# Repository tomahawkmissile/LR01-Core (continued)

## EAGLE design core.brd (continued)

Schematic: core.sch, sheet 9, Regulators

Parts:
C4, C36, C37, C38, C42, C43, C162, C175, C181: 10uF; 0603
C5, C7, C8, C12, C46, C47, C87, C152, C153, C164, C182, C184, C185, C192, C195: 0.1uF; 0603
C6, C176, C183, C198, C199: 22uF; 0603
C34, C35: 150uF; CAPPRD350W65D800H1500B
C39, C40: 1nF; 0603
C41, C45, C148, C149: 4.7uF; 0603
C44: 0.033uF; 0603
C86, C151, C163, C191: 1uF; 0603
C142, C145: 470uF; CAPPRD300W65D800H1200B
C143, C144: 270uF; CAPPRD350W65D800H1500B
C146: 220uF; CAPPRD250W65D600H1100B
C150, C167: 0.47uF; 0603
C154, C172: 100pF; 0603
C155, C165, C173: 0.01uF; 0603
C156, C171: 0.056uF; 0603
C157, C161, C174: 47uF; 0805
C159: 100uF; 0805
C166, C168: 2.2uF; 0603
C169, C170: 33pF; 0603
C193: 10uF; 0805
C194: 0.1uF; 0805
C196: 0.015uF; 0603
C197: 150pF; 0603
C200: 200pF; 0603
C216: DNI; 0603
D5, D6: Green; 0603.LED
Q8, Q9, Q10, Q11: CSD18543Q3A; SON65P300X315X90-9N
R13: 5.11R; 0603
R14: 7.15k; 0603
R15, R208, R230, R243: 100k; 0603
R16: 0.006R; 0805
R17: 3.09R; 0603
R18: DNI; 0603
R19, R20: 4.75k; 0603
R52, R229: 10k; 0603
R54: 4.7k; 0603
R202, R203, R204, R211, R212, R213: 10.2R; 0603
R205, R217: 0.005R; R2512
R206: 0R; 0603
R207: 19.6k 0.1%; 0603
R214, R215, R216: 49.9R; 0603
R218: 29.4k 1%; 0603
R219: 220R; 0603
R220: 330R; 0603
R231: 2.05k_1%; 0603
R232: 51.1R_1%; 0603
R233: 31.6k_1%; 0603
R234: 10k_1%; 0603
TP1, TP2, TP24, TP25, TP26, TP29, TP31, TP32: TESTPAD_TPSQB1,27; TESTPAD_B1,27
U4, U38: Value; YZH0016AFAF
U6: TPS51116_PWP_20; PWP20_3P4X2P4
U11, U40: Value; DRV0006A
U34: Value; RWG0040A
U35: Value; RLT0007A
U41: Value; DRC0010J
U$1, U$28, U$30: XFL4015-471MEB
U$2: IRF7821; SOIC127P600X175-8_V2
U$3: IRF7832; SOIC127P600X175-8_V2
U$4: XFL4020-102MEB
U$20, U$21: DB2441700L
U$22, U$25: XEL6030-152MEB
U$33: XEL4030-682ME_

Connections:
DDR_VREF: C44.2, U6.7 (VTTREF); also elsewhere on the board
DDR_VTT: C42.2, C43.2, U6.2 (VTT), U6.4 (VTTSNS); also elsewhere on the board
unnamed: U4.B3 (SW_2), U4.B4 (SW), U$1.P$1
unnamed: R19.1, R20.2, U6.10 (VDDQSET)
unnamed: C12.1, U6.20 (VBST)
unnamed: U6.17 (DRVL), U$3.4 (GATE)
unnamed: R13.1, U6.19 (DRVH)
unnamed: R13.2, U$2.4 (GATE)
unnamed: C12.2, U6.18 (LL), U$2.1 (SOURCE), U$2.2 (SOURCE), U$2.3 (SOURCE), U$3.5 (DRAIN), U$3.6 (DRAIN), U$3.7 (DRAIN), U$3.8 (DRAIN), U$4.V
unnamed: C39.2, R14.1, U6.15 (CS)
unnamed: C40.1, R16.2, R18.2, U$3.1 (SOURCE), U$3.2 (SOURCE), U$3.3 (SOURCE)
unnamed: C40.2, R17.1
unnamed: C151.2, U34.32 (RES)
unnamed: C152.1, U34.20 (HB1), U$21.CATHODE
unnamed: C153.2, U34.11 (HB2), U$20.CATHODE
unnamed: C152.2, Q8.1 (S), Q8.2 (S), Q8.3 (S), Q9.5-9 (D), U34.21 (SW1), U$22.P$2
unnamed: Q8.4 (G), R202.1, U34.23 (HOL1)
unnamed: R202.2, U34.22 (HO1)
unnamed: Q9.4 (G), R203.1, R204.1
unnamed: R203.2, U34.18 (LO1)
unnamed: R204.2, U34.19 (LOL1)
unnamed: R205.2, R214.2, U$22.P$1
unnamed: C169.1, R214.1, U34.27 (CS1)
unnamed: C169.2, R206.1, U34.26 (VOUT1)
unnamed: C154.2, R207.2, U34.29 (COMP1)
unnamed: C155.2, R207.1
unnamed: C156.2, U34.30 (SS1)
unnamed: C153.1, Q10.5-9 (D), Q11.1 (S), Q11.2 (S), Q11.3 (S), U34.10 (SW2), U$25.P$1
unnamed: Q11.4 (G), R211.1, U34.8 (HOL2)
unnamed: R211.2, U34.9 (HO2)
unnamed: R212.1, U34.12 (LOL2)
unnamed: R213.1, U34.13 (LO2)
unnamed: Q10.4 (G), R212.2, R213.2
unnamed: R215.2, R217.1, U$25.P$2
unnamed: C170.2, R215.1, U34.4 (CS2)
unnamed: C170.1, R216.1, U34.5 (VOUT2)
unnamed: C171.2, U34.1 (SS2)
unnamed: C173.1, R218.2
unnamed: C172.1, R218.1, U34.2 (COMP2)
unnamed: D6.P$1 (1), R219.2
unnamed: D5.P$1 (1), R220.2
unnamed: U35.6 (SW), U$28.P$1
unnamed: U38.B3 (SW_2), U38.B4 (SW), U$30.P$1
unnamed: C195.2, U41.2 (PH), U$33.P$1
unnamed: C195.1, U41.9 (BOOT)
unnamed: C196.1, R231.2
unnamed: C197.1, R231.1, U41.7 (COMP)
unnamed: C200.2, R232.1, R233.2
RESET_SOC_MPU: C8.1, C185.1, U4.D1 (VDD), U38.D1 (VDD); also elsewhere on the board
SOC_CORE: C183.2, C184.2, TP29.TP, U$30.P$2; also elsewhere on the board
SOC_I2C0_SCL: U38.D3 (SCL); also elsewhere on the board
SOC_I2C0_SDA: U38.D2 (SDA); also elsewhere on the board
SOC_I2C2_SCL: U4.D3 (SCL); also elsewhere on the board
SOC_I2C2_SDA: U4.D2 (SDA); also elsewhere on the board
SOC_MPU: C6.2, C7.2, TP1.TP, U$1.P$2; also elsewhere on the board
TPS54334_VSENSE: C200.1, R233.1, R234.2, U41.6 (VSENSE)
VCC_1V5_DDR: C34.1 (+), C35.1 (+), C38.2, R17.2, R19.2, U6.1 (VLDOIN), U6.6 (MODE), U6.9 (VDDQSNS), U$4.V1; also elsewhere on the board
VCC_1V8: C176.2, TP26.TP, U35.3 (FB), U35.4 (VOS), U$28.P$2; also elsewhere on the board
VCC_1V8_PG: R54.1, U6.11 (S3), U6.12 (S5), U35.2 (PG)
VCC_3V3_IO: C198.2, C199.2, R232.2, TP32.TP, U$33.P$2; also elsewhere on the board
VCC_3V3_PREREG: C4.2, C5.2, C142.1 (+), C143.1 (+), C157.2, C175.2, C181.2, C182.2, R52.2, R54.2, R205.1, R206.2, R208.2, R219.1, R229.2, R230.2, TP24.TP, U4.A1 (AVIN), U4.A3 (VSEL1), U4.A4 (VIN), U4.C2 (VSEL0), U11.6 (IN), U35.7 (VIN), U38.A1 (AVIN), U38.A3 (VSEL1), U38.A4 (VIN), U38.C2 (VSEL0), U40.6 (IN); also elsewhere on the board
VCC_3V3_PREREG_PG: C165.2, R208.1, U34.24 (PG1)
VCC_5V0: C39.1, C41.2, C45.2, C46.2, C47.2, C144.1 (+), C145.1 (+), C174.2, R14.2, R15.2, R216.2, R217.2, R220.1, TP25.TP, U6.8 (COMP), U6.14 (V5IN), U34.6 (VCCX); also elsewhere on the board
VCC_5V0_PG: R243.2, U34.7 (PG2)
VCC_12V0: C36.2, C37.2, C146.1 (+), C159.2, C161.2, C162.2, C163.2, C164.2, C166.1, C167.1, C168.1, C193.2, C194.2, Q8.5-9 (D), Q11.5-9 (D), U34.25 (VIN), U34.31 (EN1), U34.40 (EN2), U41.1 (VIN), U$2.5 (DRAIN), U$2.6 (DRAIN), U$2.7 (DRAIN), U$2.8 (DRAIN); also elsewhere on the board
VCC_LM5140: C148.2, C149.2, U34.15 (VCC_2), U34.16 (VCC), U$20.ANODE, U$21.ANODE
VDDA_1V8: C191.1, TP31.TP, U40.1 (OUT); also elsewhere on the board
VDDA_1V8_PG: C192.1, R229.1, U40.3 (PG)
VDDA_LM5140: C150.1, R243.1, U34.3 (FB2), U34.28 (FB1), U34.33 (DEMB), U34.34 (ILSET), U34.36 (VDDA), U34.37 (OSC)
VDDS_DDR_PGOOD: R15.1, U6.13 (PGOOD), U41.8 (EN)
VDD_CORE: U38.B1 (SENSE+); also elsewhere on the board
VDD_MPU: U4.B1 (SENSE+); also elsewhere on the board
VDD_RTC: C86.1, TP2.TP, U11.1 (OUT); also elsewhere on the board
VDD_RTC_PG: C87.1, R52.1, U11.3 (PG), U35.1 (EN), U40.4 (EN)
VIN_MON_PORZ_3V3_PG: C216.2, R230.1, U4.B2 (EN), U11.4 (EN), U38.B2 (EN), U41.10 (PGOOD); also elsewhere on the board
VSS: C4.1, C5.1, C6.1, C7.1, C8.2, C34.2 (-), C35.2 (-), C36.1, C37.1, C38.1, C41.1, C42.1, C43.1, C44.1, C45.1, C46.1, C47.1, C86.2, C87.2, C142.2 (-), C143.2 (-), C144.2 (-), C145.2 (-), C146.2 (-), C148.1, C149.1, C150.2, C151.1, C154.1, C155.1, C156.1, C157.1, C159.1, C161.1, C162.1, C163.1, C164.1, C165.1, C166.2, C167.2, C168.2, C171.1, C172.2, C173.2, C174.1, C175.1, C176.1, C181.1, C182.1, C183.1, C184.1, C185.2, C191.2, C192.2, C193.1, C194.1, C196.2, C197.2, C198.1, C199.1, C216.1, D5.P$2 (2), D6.P$2 (2), Q9.1 (S), Q9.2 (S), Q9.3 (S), Q10.1 (S), Q10.2 (S), Q10.3 (S), R16.1, R18.1, R20.1, R234.1, U4.A2 (AGND), U4.C1 (SENSE-), U4.C3 (PGND_2), U4.C4 (PGND_3), U4.D4 (PGND), U6.3 (VTTGND), U6.5 (GND), U6.16 (PGND), U6.21 (EPAD), U11.5 (GND), U11.7 (PAD), U34.14 (PGND2), U34.17 (PGND1), U34.35 (AGND), U34.38 (SYN_IN), U34.41 (DAP), U35.5 (GND), U38.A2 (AGND), U38.C1 (SENSE-), U38.C3 (PGND_2), U38.C4 (PGND_3), U38.D4 (PGND), U40.5 (GND), U40.7 (PAD), U41.3 (GND_2), U41.4 (GND_3), U41.5 (GND), U41.11 (PAD); also elsewhere on the board

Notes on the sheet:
TPS62363
TPS62087
LM5140
TPS54334
LP5912

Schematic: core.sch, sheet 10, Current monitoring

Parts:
C1, C2, C3, C9, C10, C11, C13, C29, C30, C31, C32, C33: 0.1uF; 0603
R1, R2, R4, R5, R7, R8, R10, R11: 10_1%; 0603
R3, R6, R9, R12: 0.002_1%; 1206
U3, U5, U7, U8: INA226_DGS_10; DGS10

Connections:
INA_ALERT: U3.3 (ALERT), U5.3 (ALERT), U7.3 (ALERT), U8.3 (ALERT); also elsewhere on the board
unnamed: C2.2, R2.1, U3.8 (VBUS), U3.9 (VIN-)
unnamed: C2.1, R1.1, U3.10 (VIN+)
unnamed: C10.2, R5.1, U5.8 (VBUS), U5.9 (VIN-)
unnamed: C10.1, R4.1, U5.10 (VIN+)
unnamed: C29.2, R8.1, U7.8 (VBUS), U7.9 (VIN-)
unnamed: C29.1, R7.1, U7.10 (VIN+)
unnamed: C32.2, R11.1, U8.8 (VBUS), U8.9 (VIN-)
unnamed: C32.1, R10.1, U8.10 (VIN+)
SOC_CORE: C3.1, R1.2, R3.1; also elsewhere on the board
SOC_I2C0_SCL: U3.5 (SCL), U5.5 (SCL), U7.5 (SCL), U8.2 (A0), U8.5 (SCL); also elsewhere on the board
SOC_I2C0_SDA: U3.4 (SDA), U5.4 (SDA), U7.2 (A0), U7.4 (SDA), U8.4 (SDA); also elsewhere on the board
SOC_MPU: C11.1, R4.2, R6.1; also elsewhere on the board
SOC_VDDS_DDR: R11.2, R12.2; also elsewhere on the board
VCC_1V5_DDR: C30.1, C33.1, R7.2, R9.1, R10.2, R12.1; also elsewhere on the board
VCC_3V3_IO: C1.2, C9.2, C13.2, C31.2, U3.6 (VS), U5.1 (A1), U5.6 (VS), U7.6 (VS), U8.6 (VS); also elsewhere on the board
VDDS_DDR: R8.2, R9.2; also elsewhere on the board
VDD_CORE: R2.2, R3.2; also elsewhere on the board
VDD_MPU: R5.2, R6.2; also elsewhere on the board
VSS: C1.1, C3.2, C9.1, C11.2, C13.1, C30.2, C31.1, C33.2, U3.1 (A1), U3.2 (A0), U3.7 (GND), U5.2 (A0), U5.7 (GND), U7.1 (A1), U7.7 (GND), U8.1 (A1), U8.7 (GND); also elsewhere on the board

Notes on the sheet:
I2C Address=0x40
I2C Address=0x41
I2C Address=0x42
I2C Address=0x43

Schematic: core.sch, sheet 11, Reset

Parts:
C574, C578, C579: 0.1uF; 0402
C575: 0.01uF; 0402
C577: DNI; 0402
R72: 1k; 0402
R536: 261k_1%; 0402
R537, R538, R541, R542: 10k_1%; 0402
R540: 5.81k_1%; 0402
R543: 0R; 0402
TP14: TESTPAD_TPSQB1,27; TESTPAD_B1,27
U76: Value; DDC0006A_N
U77: TPS3897_DRY_6; DRY6
U78: SN74LVC1G11_DCK_6; DCK6

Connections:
!JTAG_TRST: U78.6 (C); also elsewhere on the board
!SUPERVISOR_MASTER_RESET: R72.1, U77.1 (ENABLE); also elsewhere on the board
unnamed: C575.1, R536.1, R537.2, U76.3 (SENSE)
unnamed: C577.1, U77.5 (CT)
unnamed: R543.1, U78.4 (Y)
unnamed: R540.1, R541.2, U77.3 (SENSE)
SOC_PORZ: R543.2, TP14.TP; also elsewhere on the board
SOC_POWER_MON_PORZ: R542.1, U77.4 (SENSE_OUT), U78.1 (A)
VCC_3V3_IO: C579.1, R538.2, R542.2, U78.5 (VCC); also elsewhere on the board
VCC_3V3_PREREG: C578.2, R72.2, U77.6 (VCC); also elsewhere on the board
VCC_12V0: C574.2, R536.2, U76.5 (VDD); also elsewhere on the board
VDD_MPU: R540.2; also elsewhere on the board
VIN_MON_PORZ_3V3_PG: R538.1, U76.1 (OUT), U78.3 (B); also elsewhere on the board
VSS: C574.1, C575.2, C577.2, C578.1, C579.2, R537.1, R541.1, U76.2 (GND_2), U76.4 (GND_3), U76.6 (GND), U77.2 (GND), U78.2 (GND); also elsewhere on the board

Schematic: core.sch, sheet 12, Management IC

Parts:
C117: 0.1uF; 0402
R55, R90, R91, R94, R95, R96, R97: 10k; 0402
U12: TCA9555_RTW_24; RTW24_2P45X2P45

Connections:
!ETH_INT: R90.2, U12.2 (P01); also elsewhere on the board
!ETH_RESET: R91.2, U12.3 (P02); also elsewhere on the board
!MGMT_INT0: R94.2, U12.7 (P06); also elsewhere on the board
!MGMT_INT1: R95.2, U12.8 (P07); also elsewhere on the board
!MMC1_RESET: R97.2, U12.12; also elsewhere on the board
!MMC2_RESET: R96.2, U12.11; also elsewhere on the board
!NMI: R55.1, U12.22 (*INT); also elsewhere on the board
!USB0_OVERCURRENT: U12.4 (P03); also elsewhere on the board
!USB1_OVERCURRENT: U12.5 (P04); also elsewhere on the board
DCAN1_STB: U12.6 (P05); also elsewhere on the board
EXT_WAKEUP: U12.10; also elsewhere on the board
INA_ALERT: U12.1 (P00); also elsewhere on the board
RESET_SOC_MPU: U12.17; also elsewhere on the board
SOC_I2C0_SCL: U12.19 (SCL); also elsewhere on the board
SOC_I2C0_SDA: U12.20 (SDA); also elsewhere on the board
VCC_3V3_IO: C117.2, R55.2, R90.1, R91.1, R94.1, R95.1, R96.1, R97.1, U12.21 (VCC); also elsewhere on the board
VSS: C117.1, U12.9 (GND), U12.18 (A0), U12.23 (A1), U12.24 (A2), U12.25 (EPAD); also elsewhere on the board

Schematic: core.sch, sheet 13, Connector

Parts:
C147: 470uF; CAPPRD300W65D800H1200B
J1: SEAM-40-XX.X-XX-06-X-A

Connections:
!MGMT_INT0: J1.B26 (26); also elsewhere on the board
!MGMT_INT1: J1.B25 (25); also elsewhere on the board
!SUPERVISOR_MASTER_RESET: J1.B19 (19); also elsewhere on the board
!UART1_CTS: J1.C26 (26); also elsewhere on the board
!UART1_RTS: J1.C25 (25); also elsewhere on the board
!WARM_RESET: J1.C6 (6); also elsewhere on the board
DCAN1_H: J1.B17 (17); also elsewhere on the board
DCAN1_L: J1.B16 (16); also elsewhere on the board
EXT_WAKEUP: J1.C7 (7); also elsewhere on the board
GPIO1_16: J1.C17 (17); also elsewhere on the board
GPIO1_20: J1.C18 (18); also elsewhere on the board
GPIO1_21: J1.C19 (19); also elsewhere on the board
GPIO1_26: J1.C20 (20); also elsewhere on the board
GPIO1_27: J1.C21 (21); also elsewhere on the board
GPIO1_29: J1.C10 (10); also elsewhere on the board
GPIO2_4: J1.C9 (9); also elsewhere on the board
GPIO3_7: J1.C16 (16); also elsewhere on the board
GPIO3_8: J1.C15 (15); also elsewhere on the board
GPIO3_18: J1.C11 (11); also elsewhere on the board
GPIO3_19: J1.C12 (12); also elsewhere on the board
GPIO3_20: J1.C13 (13); also elsewhere on the board
GPIO3_21: J1.C14 (14); also elsewhere on the board
PWM0: J1.A30 (30); also elsewhere on the board
PWM1: J1.A31 (31); also elsewhere on the board
PWM2: J1.A32 (32); also elsewhere on the board
PWM3: J1.A33 (33); also elsewhere on the board
PWM4: J1.A34 (34); also elsewhere on the board
PWM5: J1.A35 (35); also elsewhere on the board
PWM6: J1.A36 (36); also elsewhere on the board
PWM7: J1.A37 (37); also elsewhere on the board
SOC_I2C2_SCL: J1.A40 (40); also elsewhere on the board
SOC_I2C2_SDA: J1.A39 (39); also elsewhere on the board
SPI0_CLK: J1.B12 (12); also elsewhere on the board
SPI0_CS0: J1.B13 (13); also elsewhere on the board
SPI0_MISO: J1.B14 (14); also elsewhere on the board
SPI0_MOSI: J1.B11 (11); also elsewhere on the board
SPI1_CLK: J1.C29 (29); also elsewhere on the board
SPI1_CS0: J1.C31 (31); also elsewhere on the board
SPI1_D0: J1.C30 (30); also elsewhere on the board
SPI1_D1: J1.C28 (28); also elsewhere on the board
TIMER4: J1.C1 (1); also elsewhere on the board
TIMER5: J1.C2 (2); also elsewhere on the board
TIMER6: J1.C3 (3); also elsewhere on the board
TIMER7: J1.C4 (4); also elsewhere on the board
UART1_RXD: J1.C24 (24); also elsewhere on the board
UART1_TXD: J1.C23 (23); also elsewhere on the board
VCC_3V3_IO: J1.B23 (23); also elsewhere on the board
VCC_5V0: J1.B21 (21); also elsewhere on the board
VCC_12V0: C147.1 (+), J1.A1 (1), J1.A2 (2), J1.A3 (3), J1.A4 (4), J1.A5 (5), J1.A6 (6), J1.A7 (7), J1.A8 (8), J1.A9 (9), J1.A10 (10); also elsewhere on the board
VSS: C147.2 (-), J1.A11 (11), J1.A12 (12), J1.A13 (13), J1.A14 (14), J1.A15 (15), J1.A16 (16), J1.A17 (17), J1.A18 (18), J1.A19 (19), J1.A20 (20), J1.A29 (29), J1.A38 (38), J1.B1 (1), J1.B2 (2), J1.B3 (3), J1.B4 (4), J1.B5 (5), J1.B6 (6), J1.B7 (7), J1.B8 (8), J1.B9 (9), J1.B10 (10), J1.B15 (15), J1.B18 (18), J1.B20 (20), J1.B22 (22), J1.B24 (24), J1.B27 (27), J1.B28 (28), J1.B29 (29), J1.B30 (30), J1.B31 (31), J1.B32 (32), J1.B33 (33), J1.B34 (34), J1.B35 (35), J1.B36 (36), J1.B37 (37), J1.B38 (38), J1.B39 (39), J1.B40 (40), J1.C5 (5), J1.C8 (8), J1.C22 (22), J1.C27 (27), J1.C32 (32); also elsewhere on the board

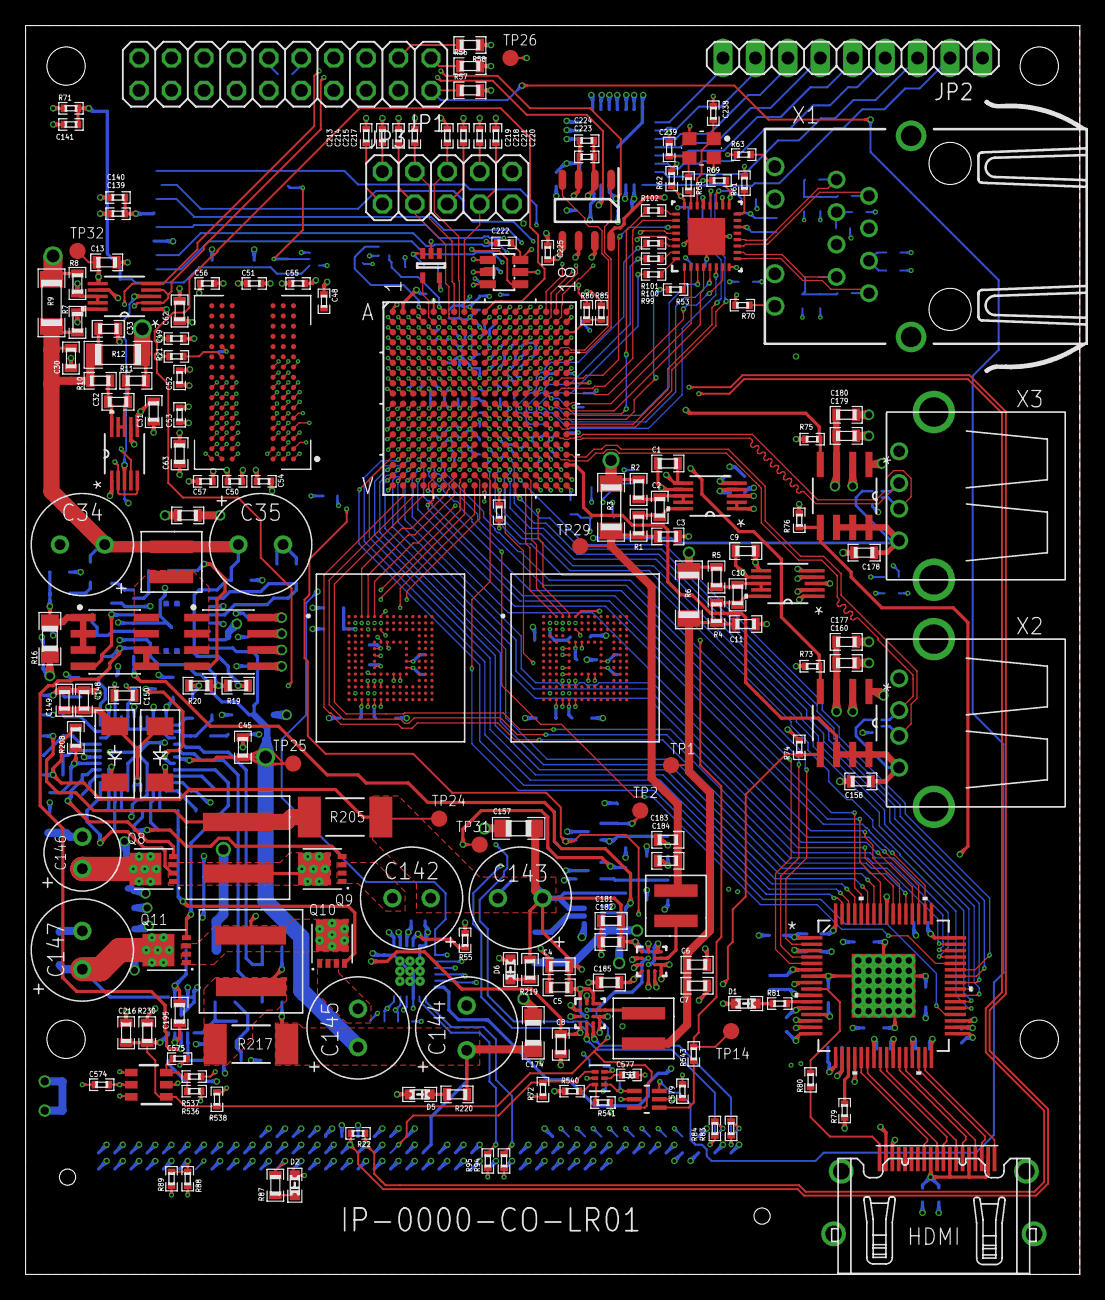
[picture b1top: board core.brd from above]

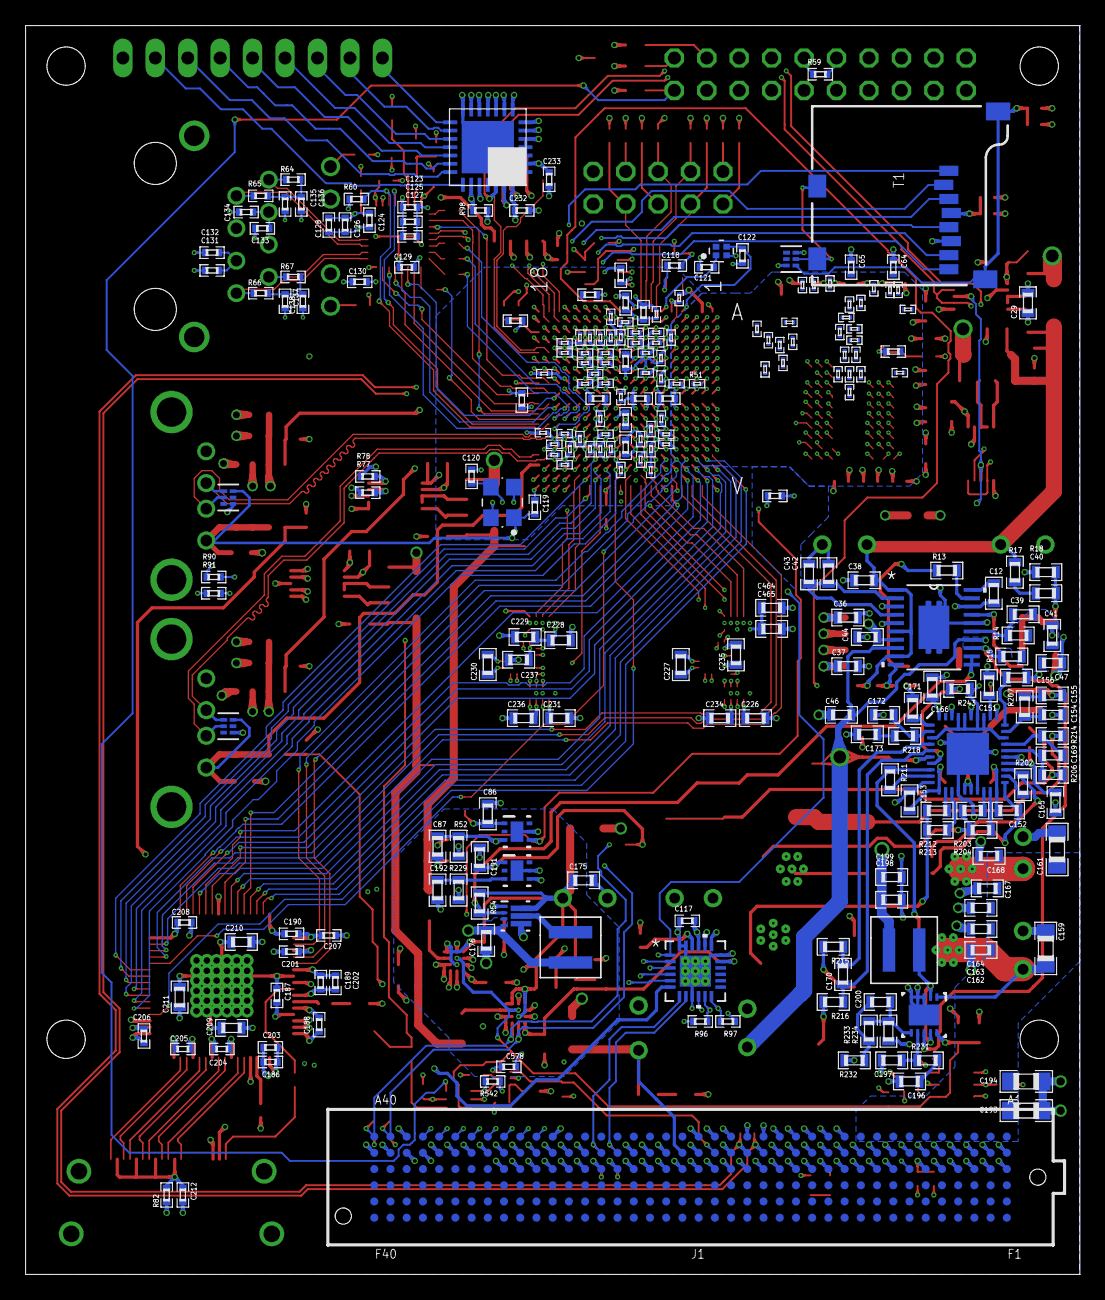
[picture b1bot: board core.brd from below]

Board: 10 copper layers, 82.5 x 97.8 mm, 446 parts (252 on the bottom side), 349 nets.

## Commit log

2019-08-08 Upload design files.
2019-08-08 Upload images.
2019-08-08 Create LICENSE
2020-01-30 Update LICENSE
